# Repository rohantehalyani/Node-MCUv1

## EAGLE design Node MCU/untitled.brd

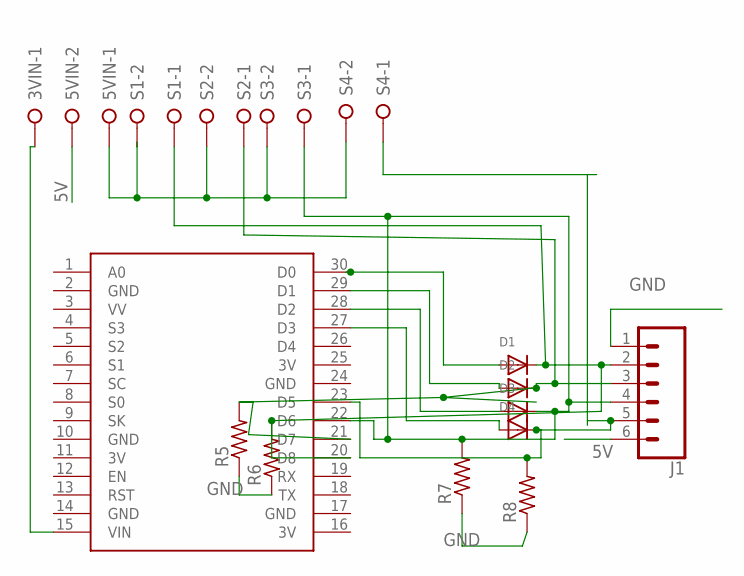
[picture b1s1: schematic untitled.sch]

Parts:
3VIN, 5VIN: W237-02P; W237-132
D1, D2, D3, D4: DIODEDO-1N4148; DO-1N4148
J1: CONN_06LONGPADS; 1X06_LONGPADS
R5, R6, R7, R8: R-US_0204/7; 0204/7
S1, S2, S3, S4: W237-02P; W237-132
U$1: NODEMCU

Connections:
3V: U$1.11 (3V), U$1.16 (3V), U$1.25 (3V)
5V: 5VIN.2, J1.6
GND: J1.1, R5.1, R6.1, R7.1, R8.1, U$1.2 (GND), U$1.10 (GND), U$1.14 (GND), U$1.17 (GND), U$1.24 (GND)
unnamed: D1.A, U$1.30 (D0)
unnamed: D2.A, U$1.29 (D1)
unnamed: D3.A, U$1.28 (D2)
unnamed: D4.A, U$1.27 (D3)
unnamed: 5VIN.1, S1.2, S2.2, S3.2, S4.2
unnamed: 3VIN.1, U$1.15 (VIN)
unnamed: D2.C, J1.3, R5.2, S2.1, U$1.21 (D7)
unnamed: D1.C, J1.2, R6.2, S1.1, U$1.20 (D8)
unnamed: D4.C, J1.5, R8.2, S4.1, U$1.23 (D5)
unnamed: D3.C, J1.4, R7.2, S3.1, U$1.22 (D6)

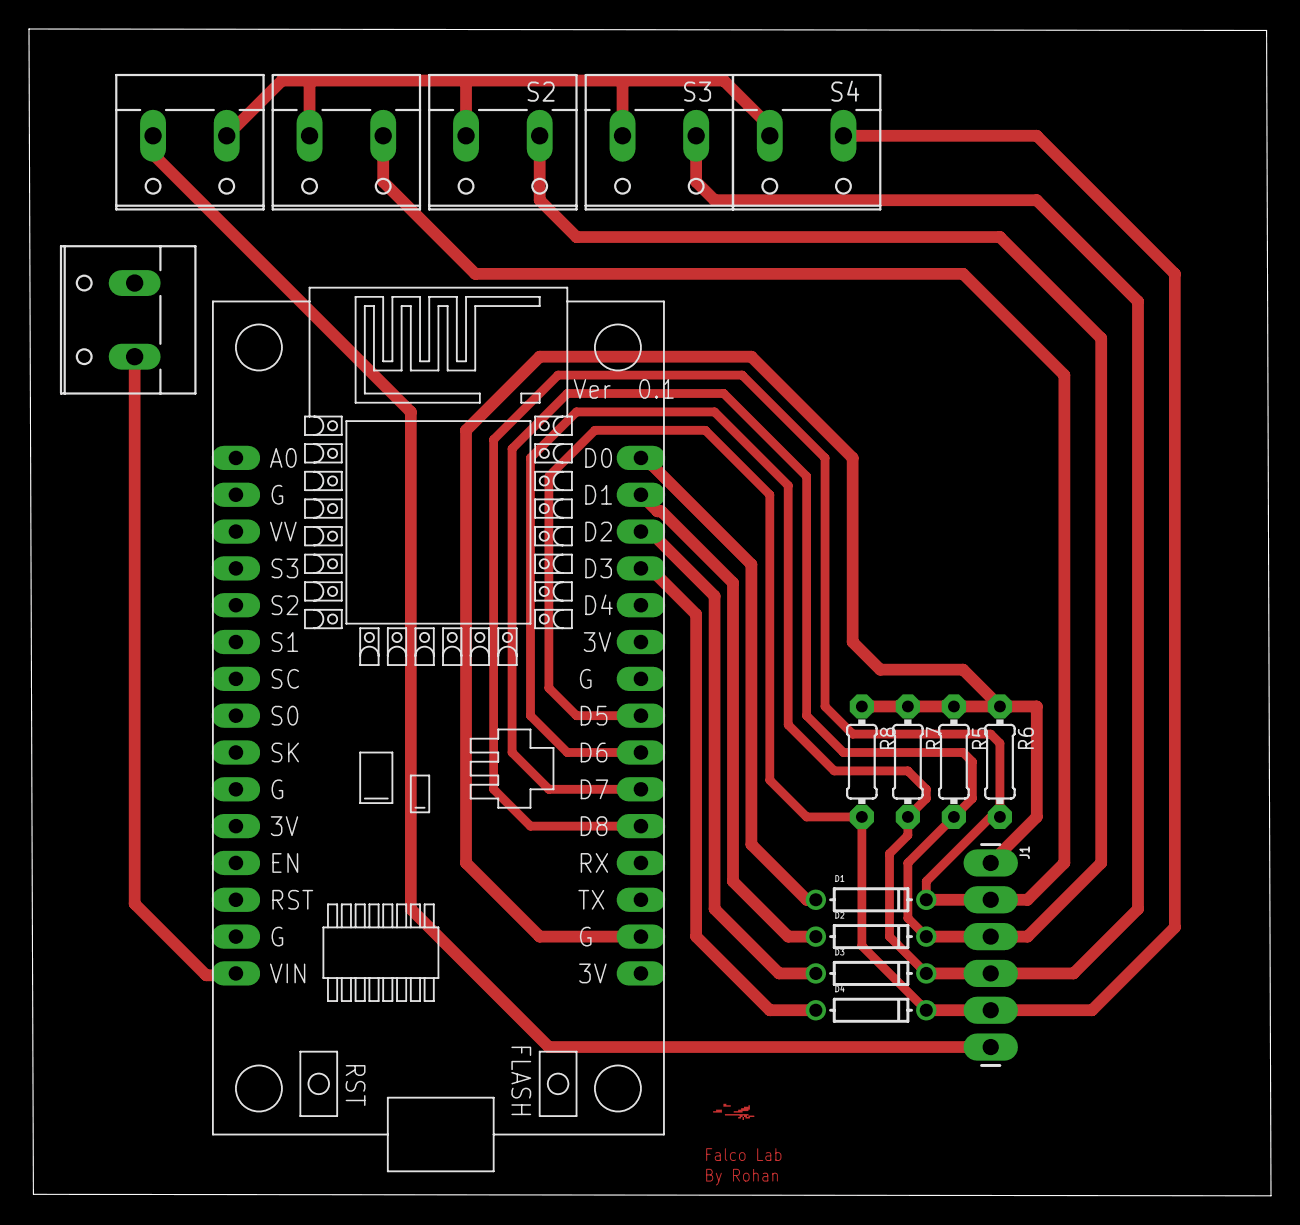
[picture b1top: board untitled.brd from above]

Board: 2 copper layers, 85.7 x 80.5 mm, 16 parts (0 on the bottom side), 13 nets.

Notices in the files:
parts and their libraries:
SparkFun-Connectors: Licensing: Creative Commons ShareAlike 4.0 International - https://creativecommons.org/licenses/by-sa/4.0
